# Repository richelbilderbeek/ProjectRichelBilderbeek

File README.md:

# ProjectRichelBilderbeek

This repository contained all Richel Bilderbeek's C++ work, 
before splitting it up in multiple smaller repositories.

See Richel Bilderbeek's current repositories or his website
to find what you are looking for.

ProjectRichelBilderbeek is scheduled for deletion at January 1st 2017.

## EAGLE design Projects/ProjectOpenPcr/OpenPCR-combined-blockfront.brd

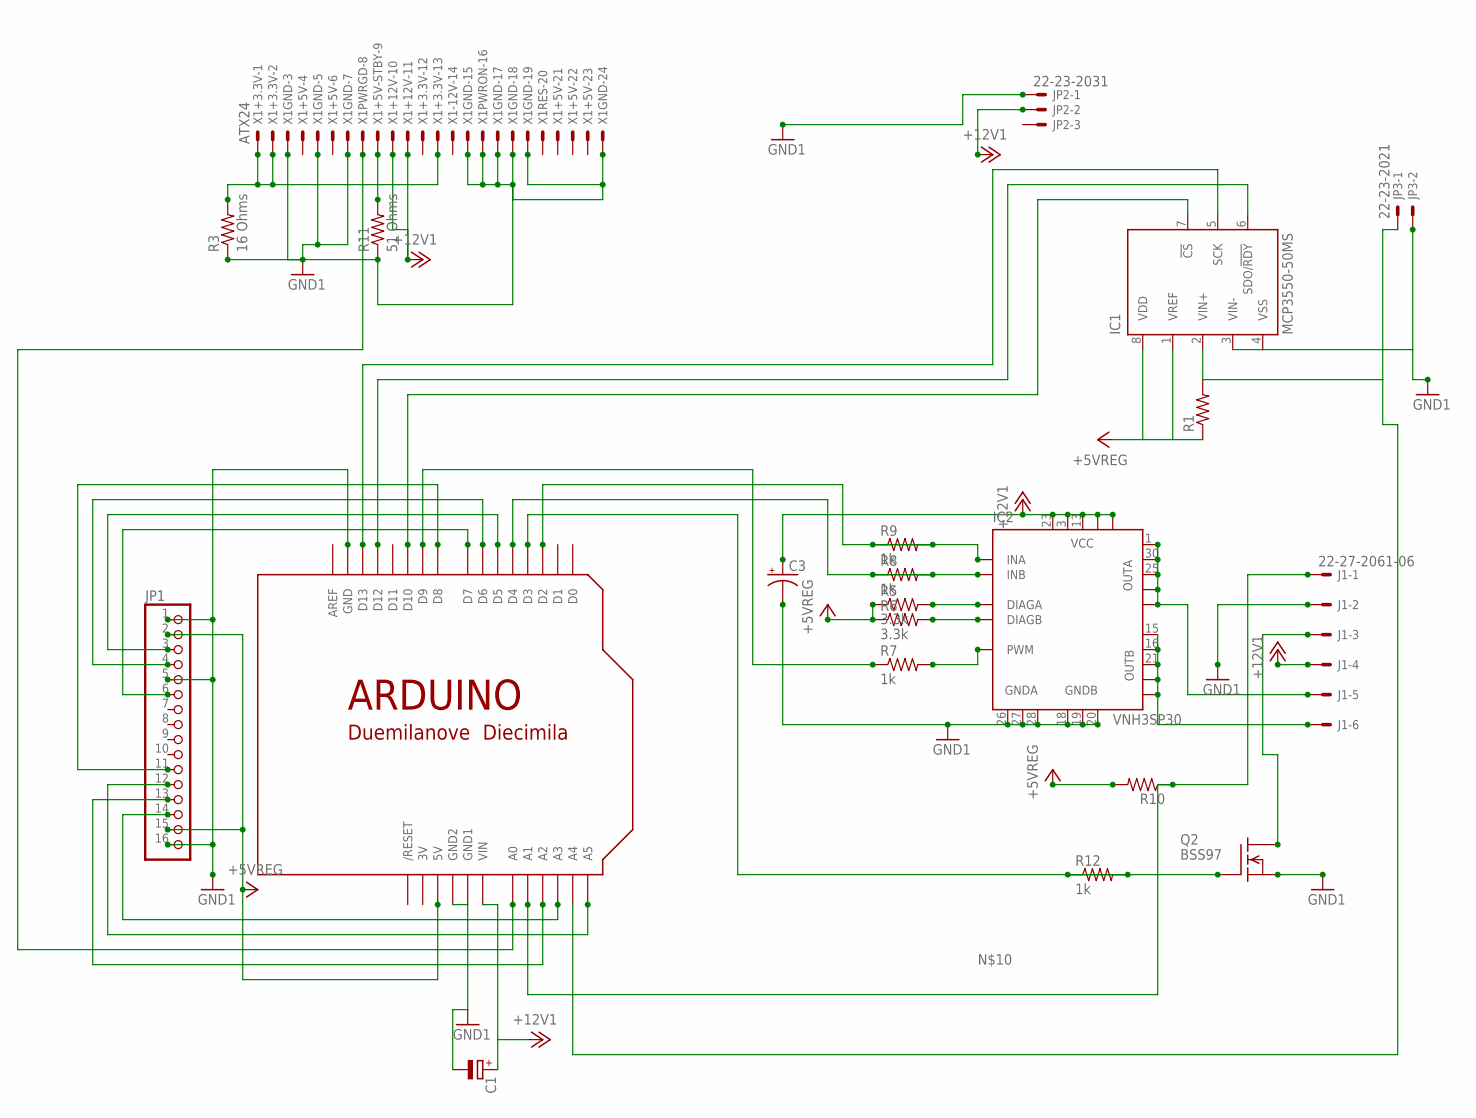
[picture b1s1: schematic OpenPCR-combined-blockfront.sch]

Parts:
C1: CPOL-EUE5-8.5; E5-8,5
C3: CPOL-USE5-13; E5-13
IC1: MCP3550-50MS; MSOP8; MPN MCP3550-50E/MS
IC2: VNH3SP30; MULTIPOWERSO-30
J1: 22-27-2061-06; 6410-06
JP1: PINHD-1X16/90; 1X16/90
JP2: 22-23-2031
JP3: 22-23-2021
Q2: BSS97; TO202
R1, R10: R-US_0207/10; 0207/10
R3: 16 Ohms; 0414/15
R5, R6: 3.3k; R0603
R7, R8, R9, R12: 1k; R0603
R11: 51 Ohms; 0207/12
U$3: ARDUINODUEMILANOVE; ARDUINO
X1: ATX24

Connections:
3V: U$3.3V
+3.3V: R3.2, X1.1, X1.2, X1.13
+5VREG: IC1.1 (VREF), IC1.8 (VDD), JP1.2, JP1.15, R1.1, R5.1, R6.1, R10.2, U$3.5V
+5VSTBY: R11.2, X1.9
+12V1: C1.+, C3.+, IC2.3 (VCC), IC2.13 (VCC), IC2.23 (VCC), IC2.VCC, IC2.VCC@1 (VCC), J1.4, JP2.2, U$3.VIN, X1.10, X1.11
GND1: C1.-, C3.-, IC1.3 (VIN-), IC1.4 (VSS), IC2.18 (GNDB), IC2.19 (GNDB), IC2.20 (GNDB), IC2.26 (GNDA), IC2.27 (GNDA), IC2.28 (GNDA), J1.2, JP1.1, JP1.5, JP1.16, JP2.1, JP3.2, Q2.1 (S), R3.1, R11.1, U$3.GND, U$3.GND1, U$3.GND2, X1.3, X1.5, X1.7, X1.15, X1.16, X1.17, X1.18, X1.19, X1.24
unnamed: U$3.A0, X1.8
unnamed: JP1.3, U$3.D5
unnamed: JP1.4, U$3.D6
unnamed: JP1.14, U$3.A3
unnamed: IC2.11 (INB), R8.1
unnamed: R12.2, U$3.D3
unnamed: JP1.13, U$3.A2
unnamed: JP1.6, U$3.D7
unnamed: JP1.12, U$3.A5
unnamed: IC1.5 (SCK), U$3.D13
unnamed: IC2.8 (PWM), R7.2
unnamed: J1.3, Q2.2 (D)
unnamed: IC2.5 (INA), R9.1
unnamed: JP1.11, U$3.D8
unnamed: IC1.2 (VIN+), JP3.1, R1.2, U$3.A4
unnamed: IC2.1 (OUTA), IC2.25 (OUTA), IC2.30 (OUTA), IC2.OUTA, IC2.OUTA@1 (OUTA), J1.5
unnamed: IC1.6 (SDO/!RDY), U$3.D12
unnamed: IC1.7 (!CS), U$3.D10
unnamed: R7.1, U$3.D9
unnamed: R8.2, U$3.D4
unnamed: IC2.15 (OUTB), IC2.16 (OUTB), IC2.21 (OUTB), IC2.OUTB, IC2.OUTB@1 (OUTB), J1.6
unnamed: R9.2, U$3.D2
unnamed: IC2.6 (DIAGA), R5.2
unnamed: IC2.10 (DIAGB), R6.2
unnamed: J1.1, R10.1, U$3.A1
T1: Q2.3 (G), R12.1

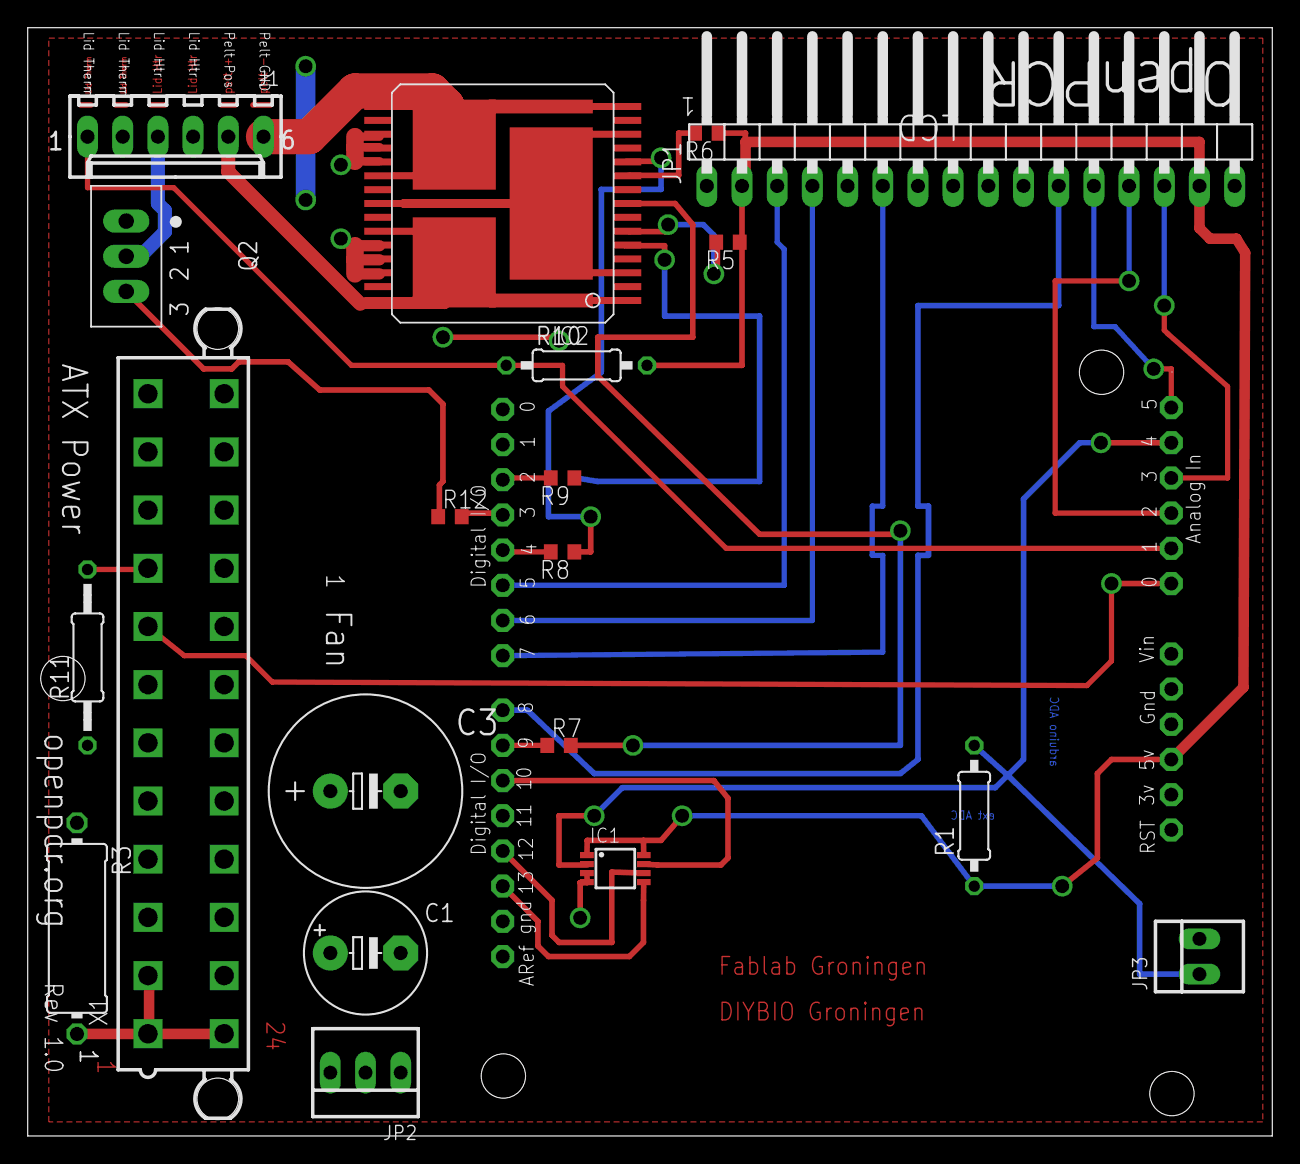
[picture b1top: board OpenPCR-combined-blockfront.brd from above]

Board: 2 copper layers, 89.8 x 80.0 mm, 21 parts (0 on the bottom side), 31 nets.

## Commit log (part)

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2015-05-03 Before chaning type of grod
2015-05-03 Before changing type of grid
2015-05-03 Changed type of grid
2015-05-03 Cleanup
2015-05-03 Before chaning Mnode to a Node*
2015-05-03 Changed Mnode to pointer
2015-05-03 Before changing TreeNode m_parent
2015-05-03 Removed useless vector
2015-05-03 Replace index by Node*
2015-05-03 Try to remove Node counter
2015-05-03 Remove Node counter
2015-05-03 Before conformizing for loops
2015-05-03 Conformizing for loops
2015-05-03 Before giving kids to a node
2015-05-03 Cleaning
2015-05-03 Greg in
2015-05-03 Can load and save
2015-05-03 Added silfide diffusion rate
2015-05-03 Checked with Fivash
2015-05-03 Progress
2015-05-04 Got it working
2015-05-04 Also install ALSA
2015-05-04 Improved Urho3d build script
2015-05-04 Added prerequisite
2015-05-04 Urho3D working
2015-05-04 Improved
2015-05-04 Added music
2015-05-04 Small refactorings
2015-05-04 Instructiontest
2015-05-04 Can move with ASDWQE
2015-05-04 With pyramid
2015-05-04 Line of cubes
2015-05-04 Sky, ground, boxes working
2015-05-04 Stand away from boxes
2015-05-05 Cleaned up
2015-05-05 3D working!
2015-05-05 Removed initial text
2015-05-05 Removed unused code
2015-05-05 ToolRosindell2008 more or less done
2015-05-05 Added correct copyright
2015-05-05 Added pics
2015-05-05 Pretty menu
2015-05-07 Added video
2015-05-07 Added
2015-05-07 Sim works, but not pretty
2015-05-07 Sim works pretty
2015-05-08 Added Brownian motion
2015-05-08 Added TestHistogram and SumBrownianMotion
2015-05-09 Start of Units
2015-05-09 Added sulfide amounts
2015-05-09 Added hydrogen molecule amounts
2015-05-09 Non-compile tests
2015-05-09 MoleculeAmount
2015-05-09 SpeciesDensity
2015-05-09 VolumetricFlow and MassFlow
2015-05-09 SpeciesDensity converts to and from file
2015-05-09 Started adding equilbrium plot
2015-05-09 Equilibrium plot shows two lines starting at high and low density
2015-05-09 Created parameter widget
2015-05-09 Created parameter widget and added it
2015-05-09 Added signal to parameter widget and respond to it
2015-05-09 Added PoiningFunction
2015-05-09 Added Consumption
2015-05-09 Fixed consumprion
2015-05-09 Fixed PoisoningFunction
2015-05-09 Fixed ConsumptionFunction
2015-05-09 Let's call it a day
2015-05-09 Nice initiaization of PRS
2015-05-09 Removing useless variables
2015-05-09 Added Loripes consumption function
2015-05-09 Added command line version
2015-05-09 Added SpeciesDensity to console version
2015-05-09 Fixed bug in SpeciesDensity
2015-05-10 Tests in place
2015-05-10 Lets call yesterday a day
2015-05-10 Renamed operator() in functions
2015-05-10 Fixed bug
2015-05-10 Fixed bug, added loripes as a state variable
2015-05-10 Added concentration
2015-05-10 Adding widgets for poisoning function
2015-05-10 Improved PoisoningFunction and use it
2015-05-10 Use PoisoningFunction in Simulation
2015-05-10 Poisoning used in GUI
2015-05-10 PoisoningFunction done
2015-05-10 Does something with full system
2015-05-10 Fixed bug: forgot s
2015-05-10 Fixed bug: set Loripes to logistic growth
2015-05-10 Removed obsolete parameter
2015-05-10 Other duties calling
2015-05-11 Conformized
2015-05-11 Added LPRSS
2015-05-12 Widget using Tab
2015-05-12 ScrollArea around parameters
2015-05-12 SpeciesGrowth
2015-05-12 Rate
2015-05-12 Species unit work well together
2015-05-12 SeagrassGrowthFunction
2015-05-12 Removed parameters from UI
2015-05-12 Added StressedLogisticGrowth
2015-05-12 Added StressedLogisticGrowth in GUI
2015-05-12 Putting in new system
2015-05-12 Moving
2015-05-12 Major refactor, kicked out all useless terms etc
2015-05-12 Added nice pics
2015-05-12 MutualismBreakdowner crosscompiles and works awesomely
2015-05-12 Minor cleanup
2015-05-12 Made screencast
2015-05-13 Extracted System from Simulation
2015-05-13 Spatial works
2015-05-13 Spatial shows something
2015-05-13 Prepare for spatial grid parameters
2015-05-13 Parameters displayed
2015-05-13 Spatial model looks pretty
2015-05-13 Can set resolution of grids
2015-05-13 Randomly kill seagrass, no diffusion yet
2015-05-13 Added colonization function
2015-05-14 Added smallest-max float-double and allow MutualismBreakdowner to crosscompile as a stand-alone
2015-05-14 Added Bat
2015-05-14 MutualismBreakdown crosscompiled
2015-05-19 Added better menu pics
2015-05-22 LPRSS allows for setting parameters
2015-05-22 LPRSS works fine
2015-05-22 Nice!
2015-05-23 Misc
2015-05-23 PRS with trait works
2015-05-24 Sim runs
2015-05-24 ProjectRichelBilderbeek v.1.20
2015-05-25 Compiles under release mode
2015-05-25 Improved TestQtEdge
2015-05-25 QtEdge clearly shows that the center node does not respond
2015-05-25 Brainweaver: red
2015-05-26 OU passes first tests
2015-05-26 Improved OU tests
2015-05-26 Brainweaver: added and passed test
2015-05-26 Improved STPP
2015-05-26 QtEdge is nice again
2015-05-26 Made more ppretty
2015-05-27 Added likelihoods to OU
2015-05-27 Renamed
2015-05-28 Seperated OU widget
2015-05-29 Likelihood BM
2015-05-29 Test likelihood
2015-05-29 Test max likelilhood
2015-05-29 Created likelikelihood widget:
2015-05-29 Created BM max likelihood widget
2015-05-29 Created BM likelihood widget
2015-06-01 Stacked bar chart in SI
2015-06-02 Put stats in SI
2015-06-03 StochasticityInspoector correctly rejects and accepts H0
2015-06-03 SI: console version
2015-06-03 SI: main dialog
2015-06-03 Renamed to HLRT
2015-06-04 Added tests
2015-06-04 Allow negative mean reversion rates
2015-06-04 Allow negative mean_reversion_rates in the likelihood
2015-06-04 Fixed StateObserver
2015-06-04 Close to solving bux
2015-06-05 Fixed bug in OU parameter estimation
2015-06-05 Added spreadsheets, fixed bugs
2015-06-05 Added unis to Brownian motion, fixed likelihood estimations
2015-06-05 Added unis to Ornstein-Uhlenbeck
2015-06-05 Added results of worked example
2015-06-06 Brainweaver: forgot adding qtnode and qtarrow to scene
2015-06-06 Fixed #274
2015-06-07 SimTopPredatorPrey works good enough
2015-06-07 Fixed #245
2015-06-07 Fixed #260
2015-06-08 Fixed bug in displaying Brownian motion
2015-06-10 RInside
2015-06-10 ribi RInside classes
2015-06-11 Status
2015-06-11 Fixed #278
2015-06-11 BD model in Treesearcher
2015-06-11 ll working
2015-06-13 Put things in namespaces
2015-06-14 Adding code to ProjectRichelBilderbeek
2015-06-14 Fixed #279
2015-06-14 ProjectRichelBilderbeek works
2015-06-16 Added Species Of The Rings
2015-06-17 Nice film
2015-06-20 Added algorithm description
2015-06-20 HistogramR
2015-06-20 Added hsitogram
2015-06-21 Brainweaver: get the concept maps running again
2015-06-21 Brainweaver progress
2015-06-23 Fix bug in PRS with trait: mutation must be in every square
2015-06-25 Brainweaver compiles again
2015-06-27 Fixed #282
2015-06-27 Fixed #190
2015-06-27 Nodes are w wef
2015-07-01 Fixed NdsMake?
2015-07-27 Nothing
2015-07-30 Added libnds:
2015-07-30 Detect absence of DEVKITPRO
2015-07-30 Adding variables (but these are incorrect)
2015-07-30 Install DevKitPro
2015-07-30 SCripts work
2015-07-31 Added desmume
2015-07-31 Desmume script
2015-08-01 Makefile in right folder
2015-08-01 No desmume in repo
2015-08-02 Added examples
2015-08-02 CppNdsExample 8: FileIO
2015-08-02 NDS work
2015-08-04 Improved scripts
2015-08-04 Removed incorrect assert
2015-08-05 Moves tests to ::Test functions
2015-08-05 Improved Node and Edge addition,removal,selection
2015-08-06 Fixed #281
2015-08-06 Fixed #209
2015-08-06 Brainweaver: green
2015-08-12 Removed View and Rate-ConceptMap
2015-08-12 Ignore -mm file
2015-08-12 Brainweaver cleanup
2015-08-13 Merged QtConceptMap and QtEditConceptMap
2015-08-20 Brainweaver: cleanup
2015-08-20 Brainweaver: moved tests to right place
2015-08-20 Added back tests
2015-08-20 Moved test to correct place
2015-08-20 Removed useless class
2015-08-20 Brainweaver: removed TODOs
2015-08-20 Removed useless FIXMEs
2015-08-21 QtRoundedRect now opaque by default
2015-08-21 Two overlapping lines have two intersection points
2015-08-21 put best GetLineLineIntersections in Geometry class
2015-08-21 Moved implementation from header to cpp in Geometry, got Brainweaver to compile again
2015-08-21 Arrows are nice again!
2015-08-21 DasWahreSchlagerfest preparing for NDS version
2015-08-22 Brainweaver: start adding commands to QtConceptMap
2015-08-24 DasWahreSchlagerfest: NDS version does something
2015-08-24 Brainweaver: can add Node by using a command
2015-08-24 Adding nodes by keyboard works nice
2015-08-24 Use grit
2015-08-24 Deletion f nodes without warnings and problems
2015-08-24 QtKeyboardFriendlyGraphicsView v1.2
2015-08-24 QtKeyboardFriendlyGraphicsView improved
2015-08-25 Improved selection
2015-08-25 Brainweaver: can create nodes and edges from keyboard
2015-08-25 Brainweaver: progress
2015-08-26 Brainweaver: can add Edge
2015-08-26 Adding a QtEdge gives correct focus and selection
2015-08-26 Brainweaver: removed redundant QtConceptMap::AddEdge member function
2015-08-26 Brainweaver: does not crash when connecting a QtEdge its QtNode with a QtNode
2015-08-26 PicToCode version 1.6
2015-08-27 DasWahreSchlagerfest runs on DS but does not look nice
2015-08-27 PicToCode version 1.7, DasWahreSchlagerfest for NDS works nice
2015-08-27 Brainweaver: can create and delete edges
2015-08-27 Brainweaver: adding and deleting nodes works perfect
2015-08-27 Added SFML script
2015-08-27 SFML working
2015-08-27 SFML
2015-08-28 Brainweaver: cleaned up ConceptMap
2015-08-28 DasWahreSchlagerfest 3.0
2015-08-28 Deletion and selection of nodes and edges works correctly
2015-08-28 Brainweaver: responds correctly to ESC
2015-08-28 Brainweaver: can delete complex topologies
2015-08-31 Retrieved QUndo* code
2015-08-31 Improved code
2015-08-31 Making Commands a derived class of QUndoCommand
2015-09-05 Brainweaver: implement QUndoStack, Maziak: improved speed
2015-09-06 Created command-line RSS feed reader
2015-09-06 QUndoCommands work in QtConceptMap
2015-09-08 QtGamepad examples added just for remembering
2015-09-11 Doublure?
2015-09-13 Allow Qt4
2015-09-14 Brainweaver: fix
2015-09-15 SFML examples
2015-09-18 Also install help
2015-09-18 Selection works better
2015-09-18 Improved testing
2015-09-18 QtKeyboardFriendlyGraphicsView v1.3
2015-09-18 TicTacToe v1.9
2015-09-26 GSL added
2015-09-27 Created GSL lite (for GCC 4.9.2), intended to partially start working with GSL
2015-09-27 For Carmentje
2015-09-28 Last update
2015-10-02 Moved away BeerWanter and BeastScripter
2015-10-02 Moved Brainweaver to own GitHub
2015-10-02 Moved StyleSheetSetter to own repo
2015-10-02 Moved TestQtKeyboardFriendlyGraphicsView to own repo
2015-10-02 Moved ToolTestQtArrowItems to own GitHub
2015-10-02 Moved TestQtRoundedEditRect to own repo
2015-10-02 Moved TestQtRoundedRectItem to own GitHub
2015-10-02 Moved Classes and Libraries to own Ribi GitHub
2015-10-02 Moved GTST to own GitHub
2015-10-02 Moved Boenken to own repo
2015-10-02 Moved ConnectThree
2015-10-02 Moved DasWahreSchlagerfest to won repo
2015-10-02 Moved DasWahreSchlagerfestNds to own repo
2015-10-02 Moved EverythingToPiecesShooter to own repo
2015-10-02 Moved K3OpEenRij to own repo
2015-10-02 Moved Maziak to own repo
2015-10-02 Moved Reversi to own repo
2015-10-02 Moved SearchAndDestroChess to its own repo
2015-10-03 Improved backup script
2015-10-03 Moved TankBattalion to own repo
2015-10-04 Moved to own repo
2015-10-04 Moved Hometrainer
2015-10-04 Moved XeNonZero to own repo
2015-10-04 Moved all games to own repo
2015-10-04 Moved all tests
2015-10-05 GitHub scripts
2015-10-09 Moved AsciiArter to own repo
2015-10-09 Moved CaesarCipher to own repo
2015-10-09 Moved CellularAutomatonZero to own repo
2015-10-09 Moved CodeToHtml to own repo
2015-10-09 Moved CreateCoalenceTree to own repo
2015-10-09 Moved CreateGlossary to own GitHub
2015-10-09 Moved CreateQtZipFile to own repo
2015-10-09 Moved DotMatrix to own repo
2015-10-09 Moved Encranger to own repo
2015-10-28 Ignore created Google Style Guide
2015-10-30 Moved FilterOperationer to own GitHub
2015-10-30 Moved FisherWrighter to own GitHub
2015-10-30 Moved FunctionPlotter to own GitHub
2015-10-30 Moved GaborFilterer to own GitHub
2015-10-30 Moved GrayCoder to own GitHub
2015-11-15 Moved PicToCode to own GitHub
2015-11-19 Moved PaperRockScissors and ndsmake to own repo
2015-11-21 Moved to own repos
2015-11-30 Moved to own GitHubs
2016-01-08 Moved all Tools to own GitHubs
2016-01-08 Moved everything to own GitHubs
